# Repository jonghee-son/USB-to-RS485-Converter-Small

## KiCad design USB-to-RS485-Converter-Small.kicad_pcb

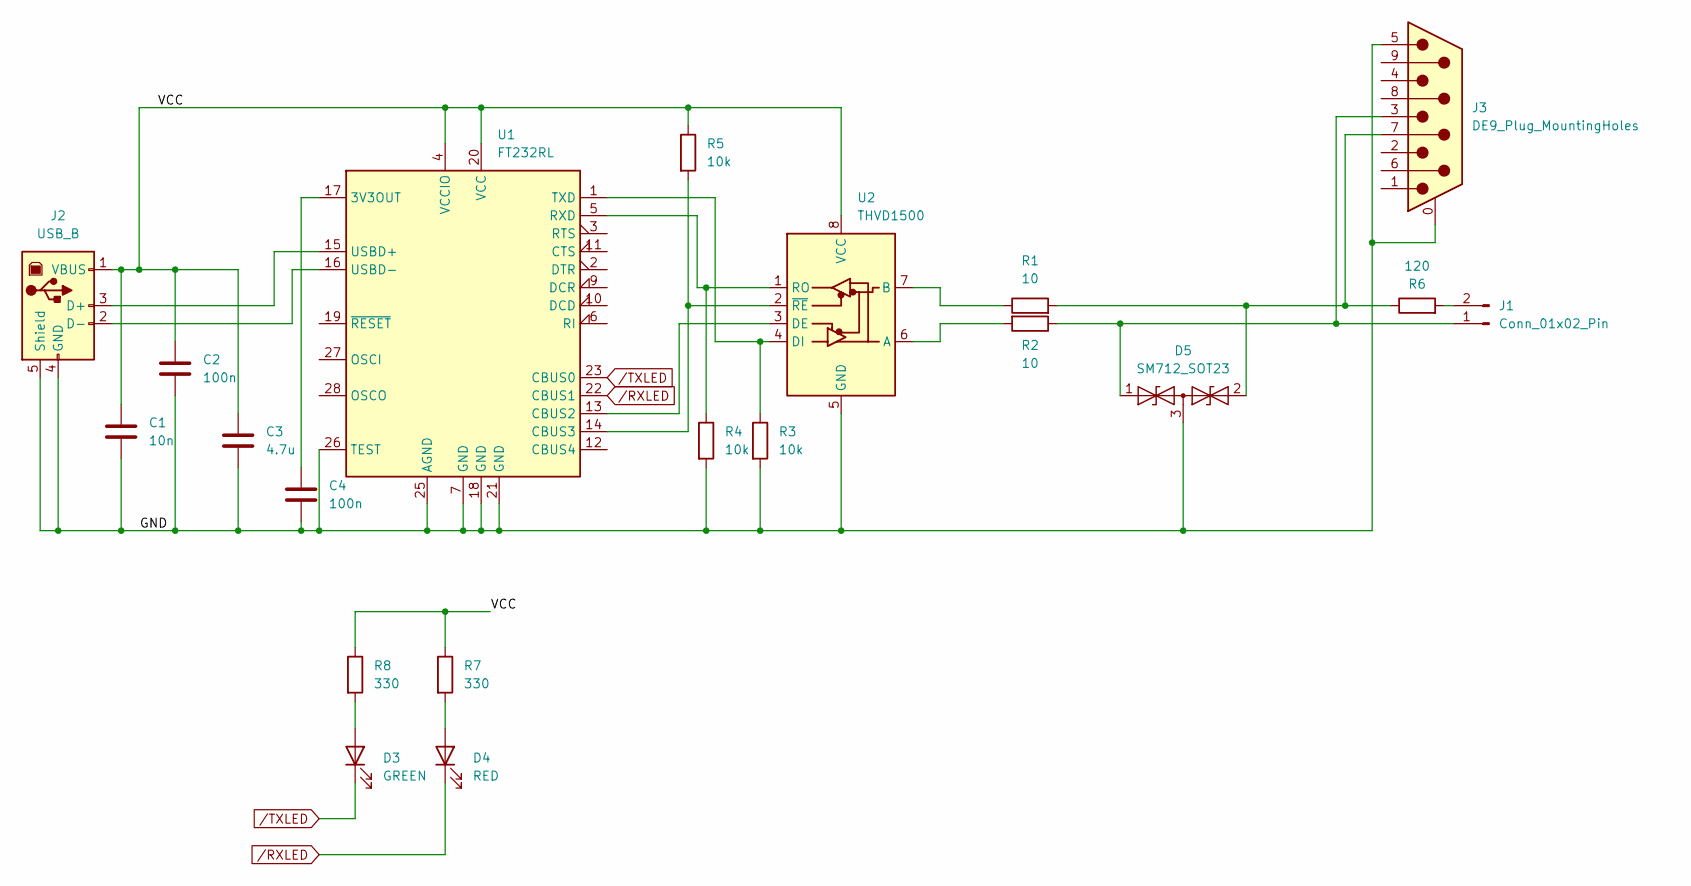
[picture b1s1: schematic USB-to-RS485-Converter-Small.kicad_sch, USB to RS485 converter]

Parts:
C1: 10n; C_0603_1608Metric_Pad1.08x0.95mm_HandSolder
C2, C4: 100n; C_0603_1608Metric_Pad1.08x0.95mm_HandSolder
C3: 4.7u; C_0603_1608Metric_Pad1.08x0.95mm_HandSolder
D3: GREEN; LED_0603_1608Metric_Pad1.05x0.95mm_HandSolder
D4: RED; LED_0603_1608Metric_Pad1.05x0.95mm_HandSolder
D5: SM712_SOT23; SOT-23
J1: Conn_01x02_Pin; PinHeader_1x02_P2.54mm_Vertical
J2: USB_B; USB_B_Lumberg_2411_02_Horizontal
J3: DE9_Plug_MountingHoles; DSUB-9_Female_Horizontal_P2.77x2.84mm_EdgePinOffset4.94mm_H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
R1, R2: 10; R_0603_1608Metric_Pad0.98x0.95mm_HandSolder
R3, R4, R5: 10k; R_0603_1608Metric_Pad0.98x0.95mm_HandSolder
R6: 120; R_0603_1608Metric_Pad0.98x0.95mm_HandSolder
R7, R8: 330; R_0603_1608Metric_Pad0.98x0.95mm_HandSolder
U1: FT232RL; SSOP-28_5.3x10.2mm_P0.65mm
U2: THVD1500; SOIC-8_3.9x4.9mm_P1.27mm

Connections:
/GND: C1.2, C2.2, C3.2, C4.2, D5.3 (common), J2.4 (GND), J2.5 (Shield), J3.0 (PAD), J3.5, R3.2, R4.2, U1.7 (GND), U1.18 (GND), U1.21 (GND), U1.25 (AGND), U1.26 (TEST), U2.5 (GND)
/VCC: C1.1, C2.1, C3.1, J2.1 (VBUS), R5.1, R7.1, R8.1, U1.4 (VCCIO), U1.20 (VCC), U2.8 (VCC)
unnamed: D3.2 (A), R8.2
unnamed: D4.2 (A), R7.2
unnamed: D5.1 (A1), J1.1, J3.3, R2.1
unnamed: D5.2 (A2), J3.7, R1.2, R6.1
unnamed: J1.2, R6.2
unnamed: J2.3 (D+), U1.15 (USBD+)
unnamed: J2.2 (D-), U1.16 (USBD-)
unnamed: C4.1, U1.17 (3V3OUT)
unnamed: U1.13 (CBUS2), U2.3 (DE)
unnamed: R5.2, U1.14 (CBUS3), U2.2 (~RE)
unnamed: R4.1, U1.5 (RXD), U2.1 (RO)
unnamed: R3.1, U1.1 (TXD), U2.4 (DI)
unnamed: R2.2, U2.6 (A)
unnamed: R1.1, U2.7 (B)
/RXLED: D4.1 (K), U1.22 (CBUS1)
/TXLED: D3.1 (K), U1.23 (CBUS0)

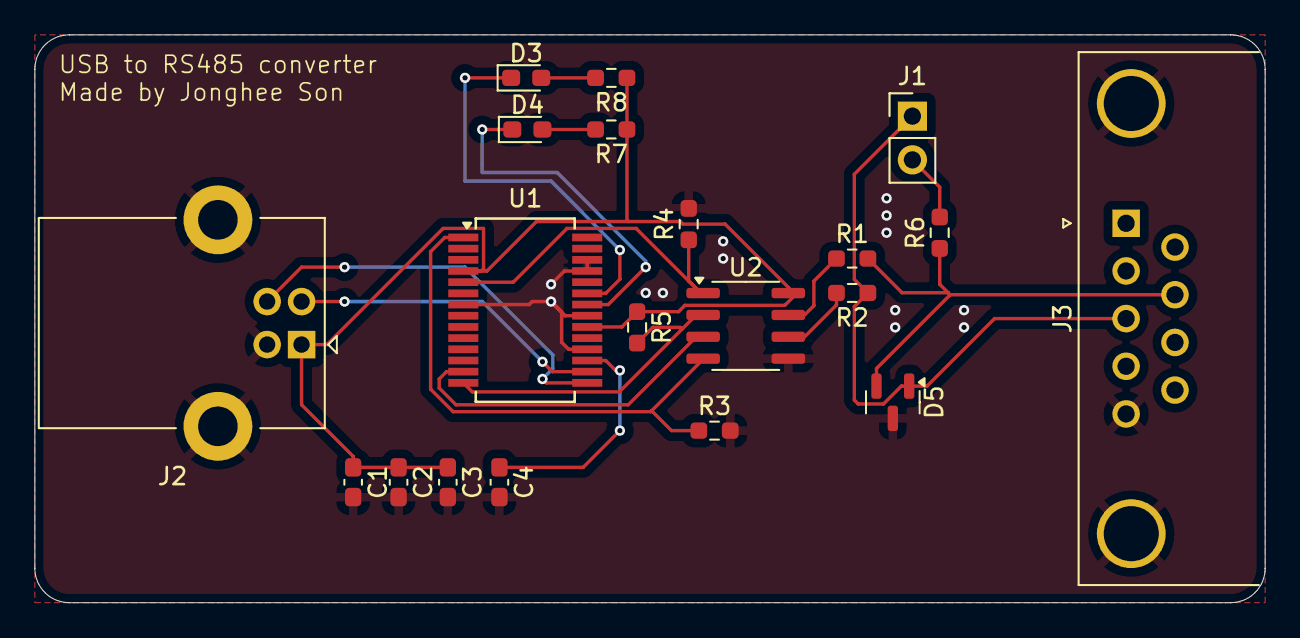
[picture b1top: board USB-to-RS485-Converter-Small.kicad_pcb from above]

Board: 4 copper layers, 71.5 x 33.0 mm, 20 parts (0 on the bottom side), 18 nets.

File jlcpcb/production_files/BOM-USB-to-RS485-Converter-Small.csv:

Comment,Designator,Footprint,LCSC
DE9_Plug_MountingHoles,J3,DSUB-9_Female_Horizontal_P2.77x2.84mm_EdgePinOffset4.94mm_Housed_MountingHolesOffset7.48mm,C141880
100n,"C2,C4",C_0603_1608Metric_Pad1.08x0.95mm_HandSolder,C14663
THVD1500,U2,SOIC-8_3.9x4.9mm_P1.27mm,C191014
4.7u,C3,C_0603_1608Metric_Pad1.08x0.95mm_HandSolder,C19666
120,R6,R_0603_1608Metric_Pad0.98x0.95mm_HandSolder,C22787
10,"R1,R2",R_0603_1608Metric_Pad0.98x0.95mm_HandSolder,C22859
330,"R7,R8",R_0603_1608Metric_Pad0.98x0.95mm_HandSolder,C23138
10k,"R3,R4,R5",R_0603_1608Metric_Pad0.98x0.95mm_HandSolder,C25804
USB_B,J2,USB_B_Lumberg_2411_02_Horizontal,C498173
SM712_SOT23,D5,SOT-23,C521963
10n,C1,C_0603_1608Metric_Pad1.08x0.95mm_HandSolder,C57112
FT232RL,U1,SSOP-28_5.3x10.2mm_P0.65mm,C8690
RED,D4,LED_0603_1608Metric_Pad1.05x0.95mm_HandSolder,C965798
GREEN,D3,LED_0603_1608Metric_Pad1.05x0.95mm_HandSolder,C965806
Conn_01x02_Pin,J1,PinHeader_1x02_P2.54mm_Vertical,

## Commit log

2024-03-20 Changed TVS diode
2024-03-20 Added designated parts for USB-B and DE9 ports
2024-05-15 Changed RS485 transceiver and TVS diode
2024-05-21 Removed choke filter
